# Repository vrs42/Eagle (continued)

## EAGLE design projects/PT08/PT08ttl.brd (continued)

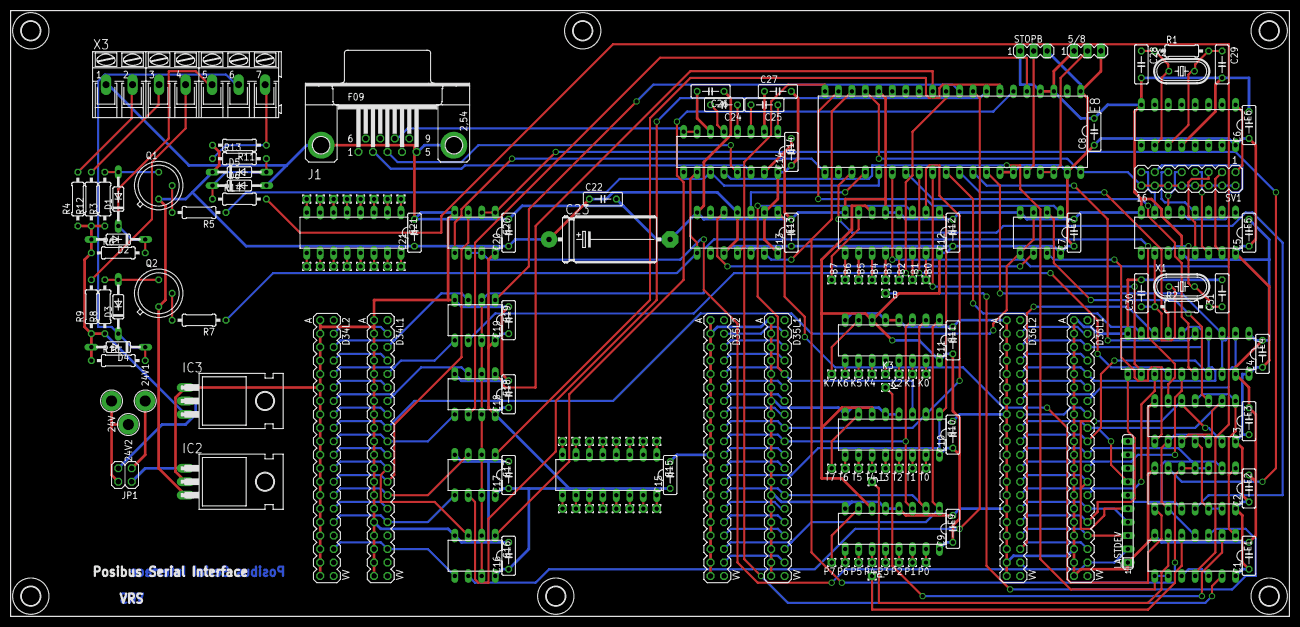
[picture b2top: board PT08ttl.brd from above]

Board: 2 copper layers, 241.3 x 114.3 mm, 168 parts (0 on the bottom side), 198 nets.

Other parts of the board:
U$1, U$2, U$3, U$4, U$5, U$6: 3,6

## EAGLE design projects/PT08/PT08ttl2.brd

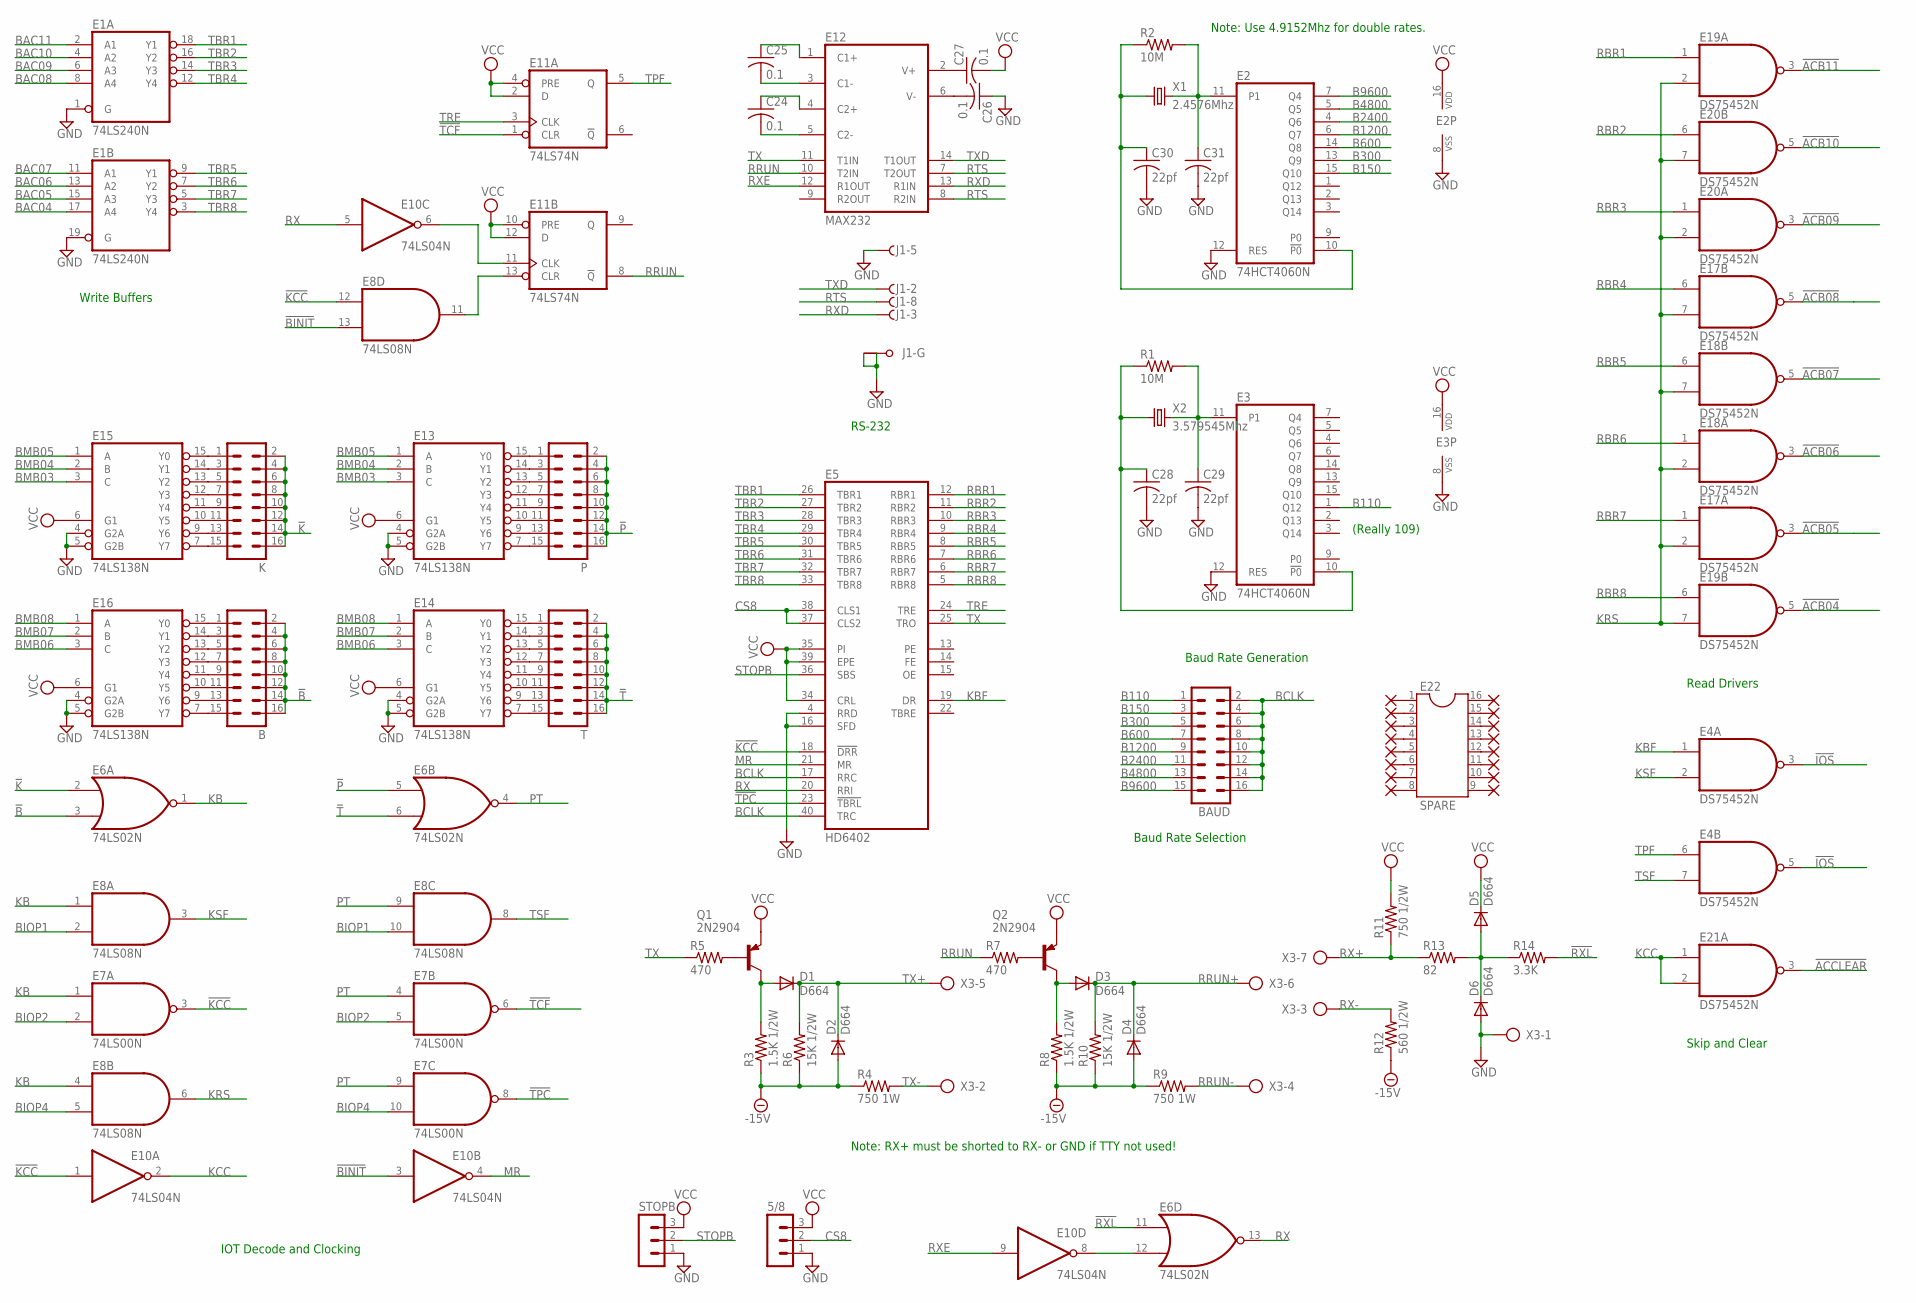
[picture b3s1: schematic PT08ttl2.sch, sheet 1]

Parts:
5/8: MA03-1
B: MA08-2
BAUD: MA08-2
C24, C25, C26, C27: 0.1; C050-025X075
C28, C29, C30, C31: 22pf; C050-025X075
D1, D2, D3, D4, D5, D6: D664; DO35-10
E1: 74LS240N; DIL20
E2, E3: 74HCT4060N; DIL16
E4, E17, E18, E19, E20, E21: DS75452N; DIL08
E5: HD6402; DIL40
E6: 74LS02N; DIL14
E7: 74LS00N; DIL14
E8: 74LS08N; DIL14
E10: 74LS04N; DIL14
E11: 74LS74N; DIL14
E12: MAX232; DIL16
E13, E14, E15, E16: 74LS138N; DIL16
E22: SPARE; DIL16
J1: F09HPS; F09HP
K: MA08-2
P: MA08-2
PAD18, PAD19, PAD28, PAD29, PAD30, PAD31, PAD32, PAD33, PAD34, PAD35, PAD36, PAD37, PAD38, PAD39, PAD40, PAD41: 1,6/0,8
Q1, Q2: 2N2904; TO39
R1, R2: 10M; 0207/10
R3, R8: 1.5K 1/2W; 0207/10
R4, R9: 750 1W; 0207/10
R5, R7: 470; 0207/10
R6, R10: 15K 1/2W; 0207/10
R11: 750 1/2W; 0207/10
R12: 560 1/2W; 0207/10
R13: 82; 0207/10
R14: 3.3K; 0207/10
STOPB: MA03-1
T: MA08-2
X1: 2.4576Mhz; HC49U-V
X2: 3.579545Mhz; HC49U-V
X3: AK300/7

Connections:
!ACB04: E19.5 (O); also elsewhere on the board
!ACB05: E17.3 (O); also elsewhere on the board
!ACB06: E18.3 (O); also elsewhere on the board
!ACB07: E18.5 (O); also elsewhere on the board
!ACB08: E17.5 (O); also elsewhere on the board
!ACB09: E20.3 (O); also elsewhere on the board
!ACB10: E20.5 (O); also elsewhere on the board
!ACB11: E19.3 (O); also elsewhere on the board
!ACCLEAR: E21.3 (O); also elsewhere on the board
!B: B.2, B.4, B.6, B.8, B.10, B.12, B.14, B.16, E6.3 (I1)
!BINIT: E8.13 (I1), E10.3 (I); also elsewhere on the board
!IOS: E4.3 (O), E4.5 (O); also elsewhere on the board
!K: E6.2 (I0), K.2, K.4, K.6, K.8, K.10, K.12, K.14, K.16
!KCC: E5.18 (!DRR), E7.3 (O), E8.12 (I0), E10.1 (I)
!P: E6.5 (I0), P.2, P.4, P.6, P.8, P.10, P.12, P.14, P.16
!RXL: E6.11 (I0), R14.2
!T: E6.6 (I1), T.2, T.4, T.6, T.8, T.10, T.12, T.14, T.16
!TCF: E7.6 (O), E11.1 (CLR)
!TPC: E5.23 (!TBRL), E7.8 (O)
-15V: D2.A, D4.A, R3.1, R4.1, R6.1, R8.1, R9.1, R10.1, R12.1; also elsewhere on the board
B110: BAUD.1, E3.1 (Q12)
B150: BAUD.3, E2.15 (Q10)
B300: BAUD.5, E2.13 (Q9)
B600: BAUD.7, E2.14 (Q8)
B1200: BAUD.9, E2.6 (Q7)
B2400: BAUD.11, E2.4 (Q6)
B4800: BAUD.13, E2.5 (Q5)
B9600: BAUD.15, E2.7 (Q4)
BAC04: E1.17 (A4); also elsewhere on the board
BAC05: E1.15 (A3); also elsewhere on the board
BAC06: E1.13 (A2); also elsewhere on the board
BAC07: E1.11 (A1); also elsewhere on the board
BAC08: E1.8 (A4); also elsewhere on the board
BAC09: E1.6 (A3); also elsewhere on the board
BAC10: E1.4 (A2); also elsewhere on the board
BAC11: E1.2 (A1); also elsewhere on the board
BCLK: BAUD.2, BAUD.4, BAUD.6, BAUD.8, BAUD.10, BAUD.12, BAUD.14, BAUD.16, E5.17 (RRC), E5.40 (TRC)
BIOP1: E8.2 (I1), E8.10 (I1); also elsewhere on the board
BIOP2: E7.2 (I1), E7.5 (I1); also elsewhere on the board
BIOP4: E7.10 (I1), E8.5 (I1); also elsewhere on the board
BMB03: E13.3 (C), E15.3 (C); also elsewhere on the board
BMB04: E13.2 (B), E15.2 (B); also elsewhere on the board
BMB05: E13.1 (A), E15.1 (A); also elsewhere on the board
BMB06: E14.3 (C), E16.3 (C); also elsewhere on the board
BMB07: E14.2 (B), E16.2 (B); also elsewhere on the board
BMB08: E14.1 (A), E16.1 (A); also elsewhere on the board
CS8: 5/8.2, E5.37 (CLS2), E5.38 (CLS1)
GND: 5/8.1, C26.1, C28.2, C29.2, C30.2, C31.2, D6.A, E1.1 (G), E1.10 (GND), E1.19 (G), E2.8 (VSS), E2.12 (RES), E3.8 (VSS), E3.12 (RES), E4.4 (GND), E5.3 (GND), E5.4 (RRD), E5.16 (SFD), E6.7 (GND), E7.7 (GND), E8.7 (GND), E10.7 (GND), E11.7 (GND), E12.15 (GND), E13.4 (G2A), E13.5 (G2B), E13.8 (GND), E14.4 (G2A), E14.5 (G2B), E14.8 (GND), E15.4 (G2A), E15.5 (G2B), E15.8 (GND), E16.4 (G2A), E16.5 (G2B), E16.8 (GND), E17.4 (GND), E18.4 (GND), E19.4 (GND), E20.4 (GND), E21.4 (GND), J1.5 (F), J1.G1, J1.G2, STOPB.1, X3.1; also elsewhere on the board
KB: E6.1 (O), E7.1 (I0), E8.1 (I0), E8.4 (I0)
KBF: E4.1 (I0), E5.19 (DR)
KCC: E10.2 (O), E21.1 (I0), E21.2 (I1)
KRS: E8.6 (O), E17.2 (I1), E17.7 (I1), E18.2 (I1), E18.7 (I1), E19.2 (I1), E19.7 (I1), E20.2 (I1), E20.7 (I1)
KSF: E4.2 (I1), E8.3 (O)
MR: E5.21 (MR), E10.4 (O)
unnamed: B.13, E16.9 (Y6)
unnamed: B.1, E16.15 (Y0)
unnamed: B.3, E16.14 (Y1)
unnamed: B.5, E16.13 (Y2)
unnamed: B.7, E16.12 (Y3)
unnamed: B.9, E16.11 (Y4)
unnamed: B.11, E16.10 (Y5)
unnamed: B.15, E16.7 (Y7)
unnamed: C29.1, E3.11 (P1), R1.2, X2.2
unnamed: C28.1, E3.10 (!P0), R1.1, X2.1
unnamed: C26.2, E12.6 (V-)
unnamed: C27.1, E12.2 (V+)
unnamed: Q1.2 (B), R5.2
unnamed: D1.A, Q1.3 (C), R3.2
unnamed: Q2.2 (B), R7.2
unnamed: D3.A, Q2.3 (C), R8.2
unnamed: C24.2, E12.5 (C2-)
unnamed: C30.1, E2.10 (!P0), R2.1, X1.1
unnamed: D5.A, D6.C, R13.2, R14.1
unnamed: C31.1, E2.11 (P1), R2.2, X1.2
unnamed: E8.11 (O), E11.13 (CLR)
unnamed: E6.12 (I1), E10.8 (O)
unnamed: E10.6 (O), E11.11 (CLK)
unnamed: C25.2, E12.3 (C1-)
unnamed: E22.1, PAD18.1
unnamed: E22.2, PAD19.1
unnamed: E22.3, PAD28.1
unnamed: C24.1, E12.4 (C2+)
unnamed: C25.1, E12.1 (C1+)
unnamed: E14.15 (Y0), T.1
unnamed: E22.4, PAD29.1
unnamed: E22.5, PAD30.1
unnamed: E22.6, PAD31.1
unnamed: E22.7, PAD32.1
unnamed: E22.8, PAD33.1
unnamed: E22.16, PAD34.1
unnamed: E22.15, PAD35.1
unnamed: E22.14, PAD36.1
unnamed: E22.13, PAD37.1
unnamed: E22.12, PAD38.1
unnamed: E22.11, PAD39.1
unnamed: E22.10, PAD40.1
unnamed: E22.9, PAD41.1
unnamed: E15.15 (Y0), K.1
unnamed: E15.14 (Y1), K.3
unnamed: E15.13 (Y2), K.5
unnamed: E15.12 (Y3), K.7
unnamed: E15.11 (Y4), K.9
unnamed: E15.10 (Y5), K.11
unnamed: E15.7 (Y7), K.15
unnamed: E15.9 (Y6), K.13
unnamed: E14.14 (Y1), T.3
unnamed: E14.13 (Y2), T.5
unnamed: E14.12 (Y3), T.7
unnamed: E14.11 (Y4), T.9
unnamed: E14.10 (Y5), T.11
unnamed: E14.7 (Y7), T.15
unnamed: E14.9 (Y6), T.13
unnamed: E13.15 (Y0), P.1
unnamed: E13.14 (Y1), P.3
unnamed: E13.13 (Y2), P.5
unnamed: E13.12 (Y3), P.7
unnamed: E13.11 (Y4), P.9
unnamed: E13.10 (Y5), P.11
unnamed: E13.7 (Y7), P.15
unnamed: E13.9 (Y6), P.13
PT: E6.4 (O), E7.4 (I0), E7.9 (I0), E8.9 (I0)
RBR1: E5.12 (RBR1), E19.1 (I0)
RBR2: E5.11 (RBR2), E20.6 (I0)
RBR3: E5.10 (RBR3), E20.1 (I0)
RBR4: E5.9 (RBR4), E17.6 (I0)
RBR5: E5.8 (RBR5), E18.6 (I0)
RBR6: E5.7 (RBR6), E18.1 (I0)
RBR7: E5.6 (RBR7), E17.1 (I0)
RBR8: E5.5 (RBR8), E19.6 (I0)
RRUN: E11.8 (!Q), E12.10 (T2IN), R7.1
RRUN+: D3.C, D4.C, R10.2, X3.6
RRUN-: R9.2, X3.4
RTS: E12.7 (T2OUT), E12.8 (R2IN), J1.8 (F)
RX: E5.20 (RRI), E6.13 (O), E10.5 (I)
RX+: R11.1, R13.1, X3.7
RX-: R12.2, X3.3
RXD: E12.13 (R1IN), J1.3 (F)
RXE: E10.9 (I), E12.12 (R1OUT)
STOPB: E5.36 (SBS), STOPB.2
TBR1: E1.18 (Y1), E5.26 (TBR1)
TBR2: E1.16 (Y2), E5.27 (TBR2)
TBR3: E1.14 (Y3), E5.28 (TBR3)
TBR4: E1.12 (Y4), E5.29 (TBR4)
TBR5: E1.9 (Y1), E5.30 (TBR5)
TBR6: E1.7 (Y2), E5.31 (TBR6)
TBR7: E1.5 (Y3), E5.32 (TBR7)
TBR8: E1.3 (Y4), E5.33 (TBR8)
TPF: E4.6 (I0), E11.5 (Q)
TRE: E5.24 (TRE), E11.3 (CLK)
TSF: E4.7 (I1), E8.8 (O)
TX: E5.25 (TRO), E12.11 (T1IN), R5.1
TX+: D1.C, D2.C, R6.2, X3.5
TX-: R4.2, X3.2
TXD: E12.14 (T1OUT), J1.2 (F)
VCC: 5/8.3, C27.2, D5.C, E1.20 (VCC), E2.16 (VDD), E3.16 (VDD), E4.8 (VCC), E5.1 (VCC), E5.34 (CRL), E5.35 (PI), E5.39 (EPE), E6.14 (VCC), E7.14 (VCC), E8.14 (VCC), E10.14 (VCC), E11.2 (D), E11.4 (PRE), E11.10 (PRE), E11.12 (D), E11.14 (VCC), E12.16 (VCC), E13.6 (G1), E13.16 (VCC), E14.6 (G1), E14.16 (VCC), E15.6 (G1), E15.16 (VCC), E16.6 (G1), E16.16 (VCC), E17.8 (VCC), E18.8 (VCC), E19.8 (VCC), E20.8 (VCC), E21.8 (VCC), Q1.1 (E), Q2.1 (E), R11.2, STOPB.3; also elsewhere on the board

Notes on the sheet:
IOT Decode and Clocking
Read Drivers
Skip and Clear
RS-232
Write Buffers
(Really 109)
Baud Rate Generation
Baud Rate Selection
Note: RX+ must be shorted to RX- or GND if TTY not used!
Note: Use 4.9152Mhz for double rates.

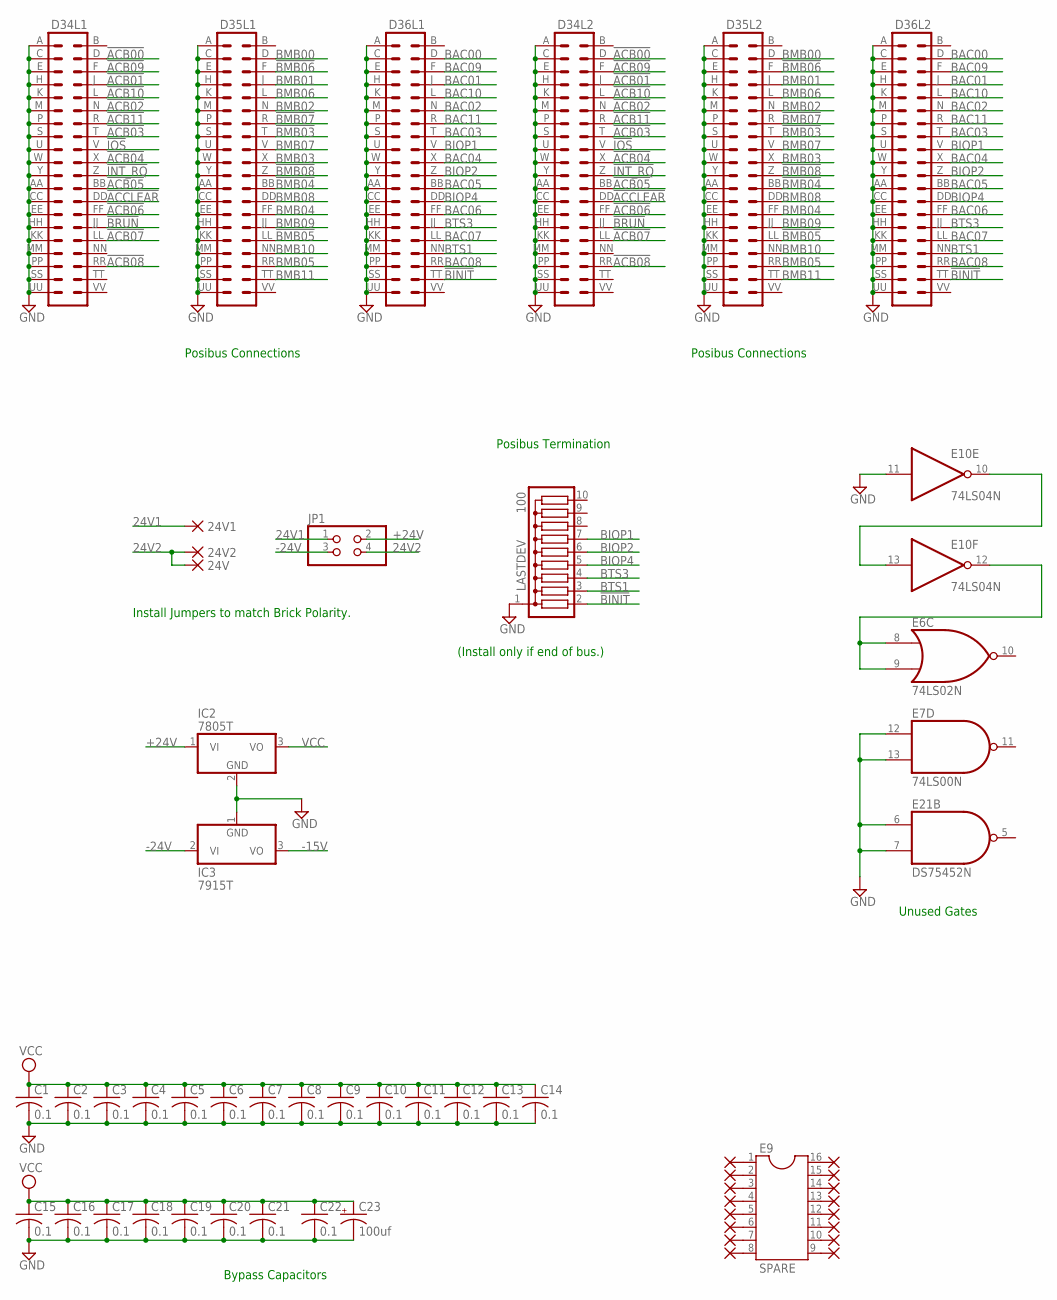
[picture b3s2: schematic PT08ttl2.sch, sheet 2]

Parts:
24V, 24V1, 24V2: PAD-0820; 0820
C1, C2, C3, C4, C5, C6, C7, C8, C9, C10, C11, C12, C13, C14, C15, C16, C17, C18, C19, C20, C21, C22: 0.1; C050-025X075
C23: 100uf; E22-9
D34L1, D34L2, D35L1, D35L2, D36L1, D36L2: DEC40PINV
E6: 74LS02N; DIL14
E7: 74LS00N; DIL14
E9: SPARE; DIL16
E10: 74LS04N; DIL14
E21: DS75452N; DIL08
IC2: 7805T; TO220H
IC3: 7915T; TO220H
JP1: PINHD-2X2; 2X02
LASTDEV: 100; SIL10
PAD1, PAD2, PAD3, PAD4, PAD5, PAD6, PAD7, PAD8, PAD9, PAD42, PAD43, PAD44, PAD45, PAD46, PAD47, PAD48: 1,6/0,8

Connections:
24V1: 24V1.P$1, JP1.1
24V2: 24V.P$1, 24V2.P$1, JP1.4
!ACB00: D34L1.D (4), D34L2.D (4)
!ACB01: D34L1.J (8), D34L2.J (8)
!ACB02: D34L1.N (12), D34L2.N (12)
!ACB03: D34L1.T (16), D34L2.T (16)
!ACB04: D34L1.X (20), D34L2.X (20); also elsewhere on the board
!ACB05: D34L1.BB (24), D34L2.BB (24); also elsewhere on the board
!ACB06: D34L1.FF (28), D34L2.FF (28); also elsewhere on the board
!ACB07: D34L1.LL (32), D34L2.LL (32); also elsewhere on the board
!ACB08: D34L1.RR (36), D34L2.RR (36); also elsewhere on the board
!ACB09: D34L1.F (6), D34L2.F (6); also elsewhere on the board
!ACB10: D34L1.L (10), D34L2.L (10); also elsewhere on the board
!ACB11: D34L1.R (14), D34L2.R (14); also elsewhere on the board
!ACCLEAR: D34L1.DD (26), D34L2.DD (26); also elsewhere on the board
!BINIT: D36L1.TT (38), D36L2.TT (38), LASTDEV.2; also elsewhere on the board
!BMB03: D35L1.T (16), D35L2.T (16)
!BMB04: D35L1.BB (24), D35L2.BB (24)
!BMB05: D35L1.LL (32), D35L2.LL (32)
!BMB06: D35L1.F (6), D35L2.F (6)
!BMB07: D35L1.R (14), D35L2.R (14)
!BMB08: D35L1.Z (22), D35L2.Z (22)
!BRUN: D34L1.JJ (30), D34L2.JJ (30)
!INT_RQ: D34L1.Z (22), D34L2.Z (22)
!IOS: D34L1.V (18), D34L2.V (18); also elsewhere on the board
+24V: IC2.1 (VI), JP1.2
-15V: IC3.3 (VO); also elsewhere on the board
-24V: IC3.2 (VI), JP1.3
BAC00: D36L1.D (4), D36L2.D (4)
BAC01: D36L1.J (8), D36L2.J (8)
BAC02: D36L1.N (12), D36L2.N (12)
BAC03: D36L1.T (16), D36L2.T (16)
BAC04: D36L1.X (20), D36L2.X (20); also elsewhere on the board
BAC05: D36L1.BB (24), D36L2.BB (24); also elsewhere on the board
BAC06: D36L1.FF (28), D36L2.FF (28); also elsewhere on the board
BAC07: D36L1.LL (32), D36L2.LL (32); also elsewhere on the board
BAC08: D36L1.RR (36), D36L2.RR (36); also elsewhere on the board
BAC09: D36L1.F (6), D36L2.F (6); also elsewhere on the board
BAC10: D36L1.L (10), D36L2.L (10); also elsewhere on the board
BAC11: D36L1.R (14), D36L2.R (14); also elsewhere on the board
BIOP1: D36L1.V (18), D36L2.V (18), LASTDEV.7; also elsewhere on the board
BIOP2: D36L1.Z (22), D36L2.Z (22), LASTDEV.6; also elsewhere on the board
BIOP4: D36L1.DD (26), D36L2.DD (26), LASTDEV.5; also elsewhere on the board
BMB00: D35L1.D (4), D35L2.D (4)
BMB01: D35L1.J (8), D35L2.J (8)
BMB02: D35L1.N (12), D35L2.N (12)
BMB03: D35L1.X (20), D35L2.X (20); also elsewhere on the board
BMB04: D35L1.FF (28), D35L2.FF (28); also elsewhere on the board
BMB05: D35L1.RR (36), D35L2.RR (36); also elsewhere on the board
BMB06: D35L1.L (10), D35L2.L (10); also elsewhere on the board
BMB07: D35L1.V (18), D35L2.V (18); also elsewhere on the board
BMB08: D35L1.DD (26), D35L2.DD (26); also elsewhere on the board
BMB09: D35L1.JJ (30), D35L2.JJ (30)
BMB10: D35L1.NN (34), D35L2.NN (34)
BMB11: D35L1.TT (38), D35L2.TT (38)
BTS1: D36L1.NN (34), D36L2.NN (34), LASTDEV.3
BTS3: D36L1.JJ (30), D36L2.JJ (30), LASTDEV.4
GND: C1.2, C2.2, C3.2, C4.2, C5.2, C6.2, C7.2, C8.2, C9.2, C10.2, C11.2, C12.2, C13.2, C14.2, C15.2, C16.2, C17.2, C18.2, C19.2, C20.2, C21.2, C22.2, C23.-, D34L1.A (1), D34L1.AA (23), D34L1.C (3), D34L1.CC (25), D34L1.E (5), D34L1.EE (27), D34L1.H (7), D34L1.HH (29), D34L1.K (9), D34L1.KK (31), D34L1.M (11), D34L1.MM (33), D34L1.P (13), D34L1.PP (35), D34L1.S (15), D34L1.SS (37), D34L1.U (17), D34L1.UU (39), D34L1.W (19), D34L1.Y (21), D34L2.A (1), D34L2.AA (23), D34L2.C (3), D34L2.CC (25), D34L2.E (5), D34L2.EE (27), D34L2.H (7), D34L2.HH (29), D34L2.K (9), D34L2.KK (31), D34L2.M (11), D34L2.MM (33), D34L2.P (13), D34L2.PP (35), D34L2.S (15), D34L2.SS (37), D34L2.U (17), D34L2.UU (39), D34L2.W (19), D34L2.Y (21), D35L1.A (1), D35L1.AA (23), D35L1.C (3), D35L1.CC (25), D35L1.E (5), D35L1.EE (27), D35L1.H (7), D35L1.HH (29), D35L1.K (9), D35L1.KK (31), D35L1.M (11), D35L1.MM (33), D35L1.P (13), D35L1.PP (35), D35L1.S (15), D35L1.SS (37), D35L1.U (17), D35L1.UU (39), D35L1.W (19), D35L1.Y (21), D35L2.A (1), D35L2.AA (23), D35L2.C (3), D35L2.CC (25), D35L2.E (5), D35L2.EE (27), D35L2.H (7), D35L2.HH (29), D35L2.K (9), D35L2.KK (31), D35L2.M (11), D35L2.MM (33), D35L2.P (13), D35L2.PP (35), D35L2.S (15), D35L2.SS (37), D35L2.U (17), D35L2.UU (39), D35L2.W (19), D35L2.Y (21), D36L1.A (1), D36L1.AA (23), D36L1.C (3), D36L1.CC (25), D36L1.E (5), D36L1.EE (27), D36L1.H (7), D36L1.HH (29), D36L1.K (9), D36L1.KK (31), D36L1.M (11), D36L1.MM (33), D36L1.P (13), D36L1.PP (35), D36L1.S (15), D36L1.SS (37), D36L1.U (17), D36L1.UU (39), D36L1.W (19), D36L1.Y (21), D36L2.A (1), D36L2.AA (23), D36L2.C (3), D36L2.CC (25), D36L2.E (5), D36L2.EE (27), D36L2.H (7), D36L2.HH (29), D36L2.K (9), D36L2.KK (31), D36L2.M (11), D36L2.MM (33), D36L2.P (13), D36L2.PP (35), D36L2.S (15), D36L2.SS (37), D36L2.U (17), D36L2.UU (39), D36L2.W (19), D36L2.Y (21), E6.7 (GND), E7.7 (GND), E7.12 (I0), E7.13 (I1), E10.7 (GND), E10.11 (I), E21.4 (GND), E21.6 (I0), E21.7 (I1), IC2.2 (GND), IC3.1 (GND), LASTDEV.1; also elsewhere on the board
unnamed: E9.1, PAD1.1
unnamed: E9.2, PAD2.1
unnamed: E9.3, PAD3.1
unnamed: E9.4, PAD4.1
unnamed: E9.5, PAD5.1
unnamed: E10.10 (O), E10.13 (I)
unnamed: E9.6, PAD6.1
unnamed: E9.7, PAD7.1
unnamed: E9.8, PAD8.1
unnamed: E9.16, PAD9.1
unnamed: E9.15, PAD42.1
unnamed: E9.14, PAD43.1
unnamed: E9.13, PAD44.1
unnamed: E9.12, PAD45.1
unnamed: E9.11, PAD46.1
unnamed: E9.10, PAD47.1
unnamed: E9.9, PAD48.1
unnamed: E6.8 (I0), E6.9 (I1), E10.12 (O)
VCC: C1.1, C2.1, C3.1, C4.1, C5.1, C6.1, C7.1, C8.1, C9.1, C10.1, C11.1, C12.1, C13.1, C14.1, C15.1, C16.1, C17.1, C18.1, C19.1, C20.1, C21.1, C22.1, C23.+, E6.14 (VCC), E7.14 (VCC), E10.14 (VCC), E21.8 (VCC), IC2.3 (VO); also elsewhere on the board

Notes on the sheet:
Bypass Capacitors
Posibus Connections
Posibus Termination
(Install only if end of bus.)
Install Jumpers to match Brick Polarity.
Unused Gates

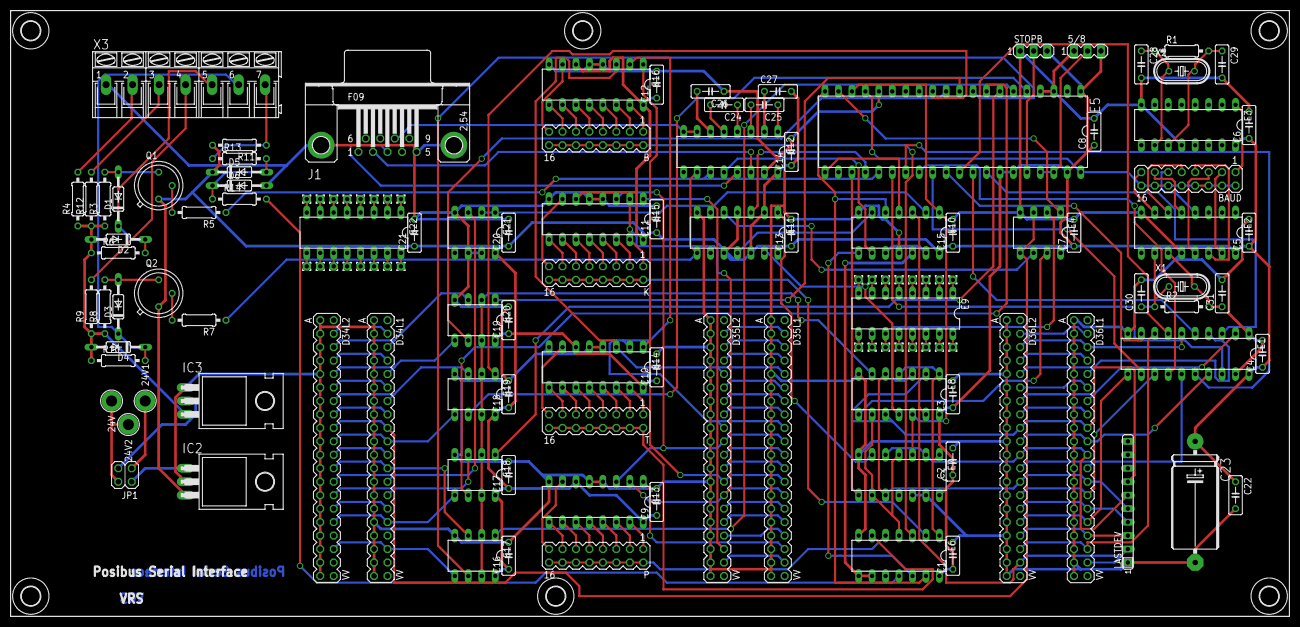
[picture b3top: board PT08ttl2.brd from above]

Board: 2 copper layers, 241.3 x 114.3 mm, 137 parts (0 on the bottom side), 201 nets.

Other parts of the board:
U$1, U$2, U$3, U$4, U$5, U$6: 3,6

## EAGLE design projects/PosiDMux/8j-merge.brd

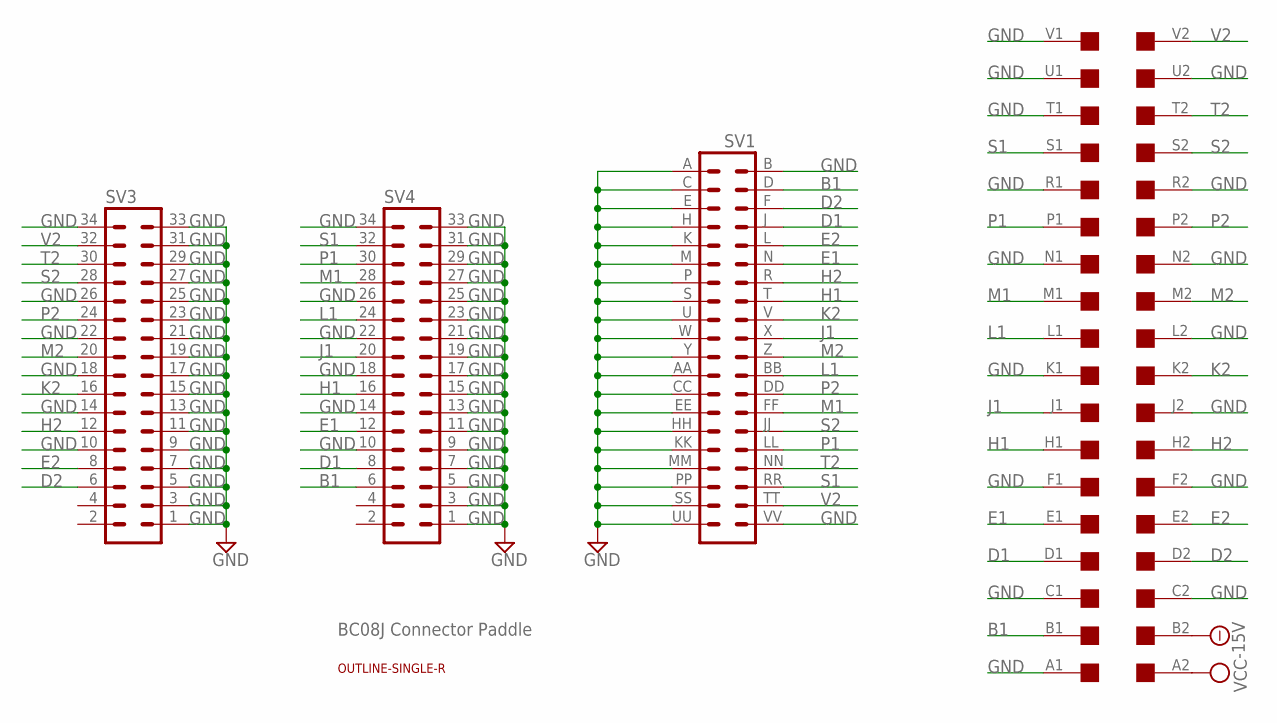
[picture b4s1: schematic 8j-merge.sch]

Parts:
SV1: DEC40PINV
SV3, SV4: MA17-2
U$1: OUTLINE-SINGLE-R; SINGLE-R
U$2: SINGLE; EDGE-CON2

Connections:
-15V: U$2.B2
B1: SV1.D (4), SV4.6, U$2.B1
D1: SV1.J (8), SV4.8, U$2.D1
D2: SV1.F (6), SV3.6, U$2.D2
E1: SV1.N (12), SV4.12, U$2.E1
E2: SV1.L (10), SV3.8, U$2.E2
GND: SV1.A (1), SV1.AA (23), SV1.B (2), SV1.C (3), SV1.CC (25), SV1.E (5), SV1.EE (27), SV1.H (7), SV1.HH (29), SV1.K (9), SV1.KK (31), SV1.M (11), SV1.MM (33), SV1.P (13), SV1.PP (35), SV1.S (15), SV1.SS (37), SV1.U (17), SV1.UU (39), SV1.VV (40), SV1.W (19), SV1.Y (21), SV3.1, SV3.3, SV3.5, SV3.7, SV3.9, SV3.10, SV3.11, SV3.13, SV3.14, SV3.15, SV3.17, SV3.18, SV3.19, SV3.21, SV3.22, SV3.23, SV3.25, SV3.26, SV3.27, SV3.29, SV3.31, SV3.33, SV3.34, SV4.1, SV4.3, SV4.5, SV4.7, SV4.9, SV4.10, SV4.11, SV4.13, SV4.14, SV4.15, SV4.17, SV4.18, SV4.19, SV4.21, SV4.22, SV4.23, SV4.25, SV4.26, SV4.27, SV4.29, SV4.31, SV4.33, SV4.34, U$2.A1, U$2.C1, U$2.C2, U$2.F1, U$2.F2, U$2.J2, U$2.K1, U$2.L2, U$2.N1, U$2.N2, U$2.R1, U$2.R2, U$2.T1, U$2.U1, U$2.U2, U$2.V1
H1: SV1.T (16), SV4.16, U$2.H1
H2: SV1.R (14), SV3.12, U$2.H2
J1: SV1.X (20), SV4.20, U$2.J1
K2: SV1.V (18), SV3.16, U$2.K2
L1: SV1.BB (24), SV4.24, U$2.L1
M1: SV1.FF (28), SV4.28, U$2.M1
M2: SV1.Z (22), SV3.20, U$2.M2
P1: SV1.LL (32), SV4.30, U$2.P1
P2: SV1.DD (26), SV3.24, U$2.P2
S1: SV1.RR (36), SV4.32, U$2.S1
S2: SV1.JJ (30), SV3.28, U$2.S2
T2: SV1.NN (34), SV3.30, U$2.T2
V2: SV1.TT (38), SV3.32, U$2.V2
VCC: U$2.A2

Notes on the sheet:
BC08J Connector Paddle

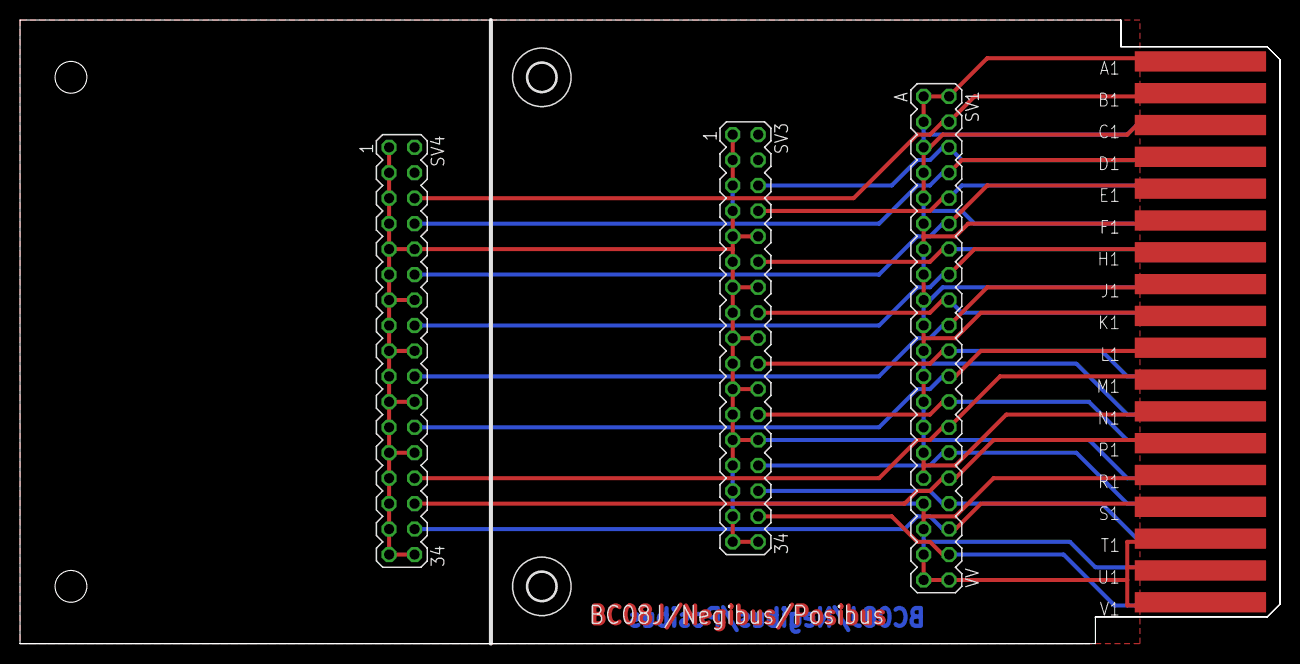
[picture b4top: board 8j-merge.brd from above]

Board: 2 copper layers, 125.7 x 62.2 mm, 7 parts (0 on the bottom side), 19 nets.

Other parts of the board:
U$3, U$4: 2,8

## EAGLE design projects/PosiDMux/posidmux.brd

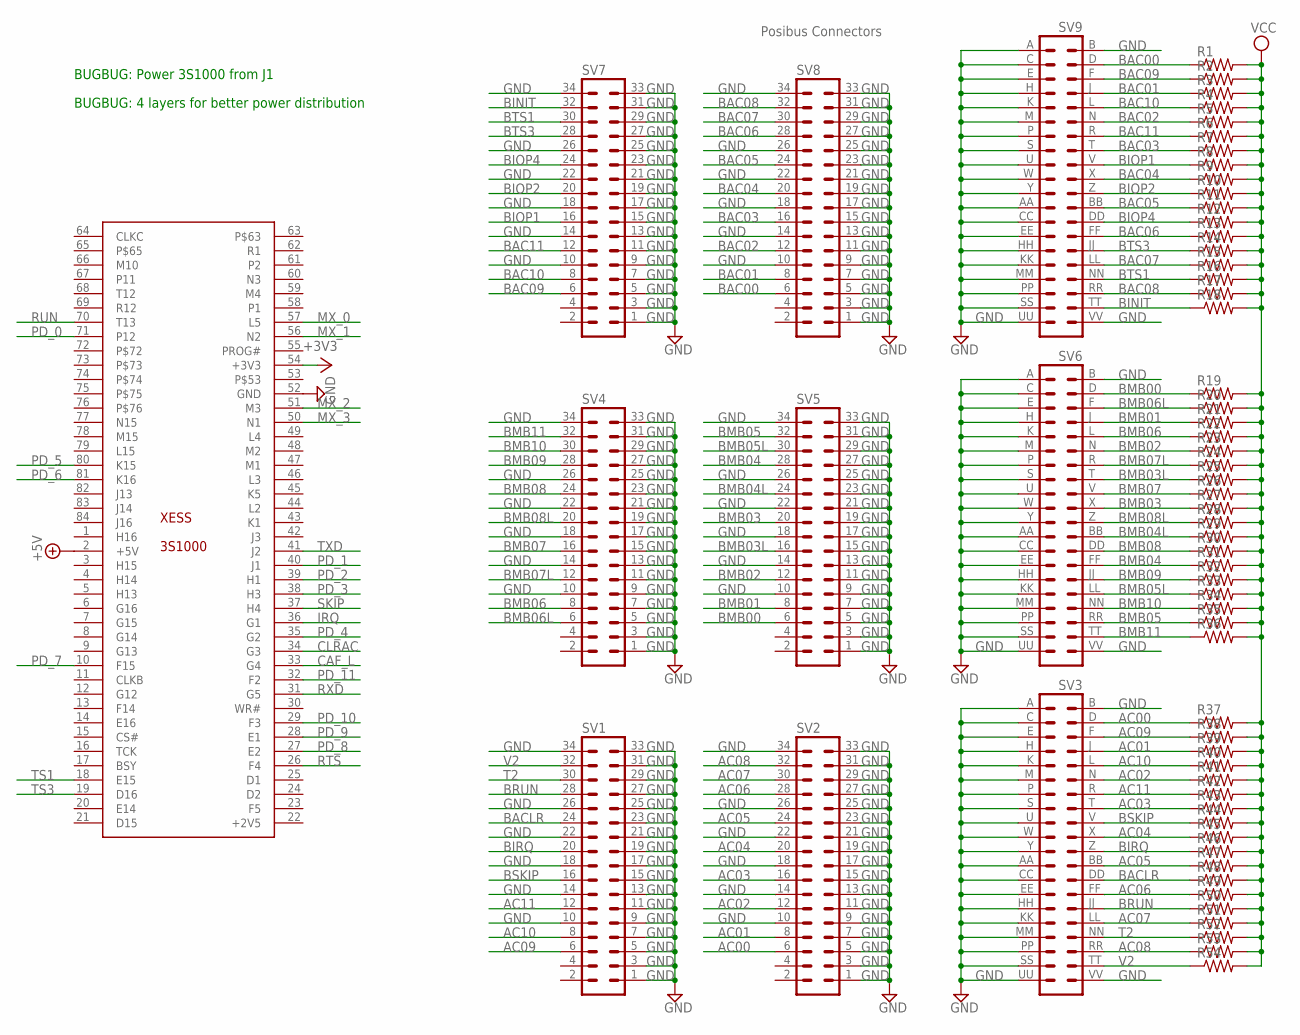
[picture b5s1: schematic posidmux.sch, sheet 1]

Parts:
R1, R2, R3, R4, R5, R6, R7, R8, R9, R10, R11, R12, R13, R14, R15, R16, R17, R18, R19, R20, R21, R22, R23, R24, R25, R26, R27, R28, R29, R30, R31, R32, R33, R34, R35, R36, R37, R38, R39, R40, R41, R42, R43, R44, R45, R46, R47, R48, R49, R50, R51, R52, R53, R54: R-US_0207/10; 0207/10
SV1, SV2, SV4, SV5, SV7, SV8: MA17-2
SV3, SV6, SV9: DEC40PINV
XESS: 3S1000

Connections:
+2V5: XESS.22 (+2V5)
+3V3: XESS.54 (+3V3); also elsewhere on the board
+5V: XESS.2 (+5V)
AC00: R37.1, SV2.6, SV3.D (4); also elsewhere on the board
AC01: R39.1, SV2.8, SV3.J (8); also elsewhere on the board
AC02: R41.1, SV2.12, SV3.N (12); also elsewhere on the board
AC03: R43.1, SV2.16, SV3.T (16); also elsewhere on the board
AC04: R45.1, SV2.20, SV3.X (20); also elsewhere on the board
AC05: R47.1, SV2.24, SV3.BB (24); also elsewhere on the board
AC06: R49.1, SV2.28, SV3.FF (28); also elsewhere on the board
AC07: R51.1, SV2.30, SV3.LL (32); also elsewhere on the board
AC08: R53.1, SV2.32, SV3.RR (36); also elsewhere on the board
AC09: R38.1, SV1.6, SV3.F (6); also elsewhere on the board
AC10: R40.1, SV1.8, SV3.L (10); also elsewhere on the board
AC11: R42.1, SV1.12, SV3.R (14); also elsewhere on the board
BAC00: R1.1, SV8.6, SV9.D (4); also elsewhere on the board
BAC01: R3.1, SV8.8, SV9.J (8); also elsewhere on the board
BAC02: R5.1, SV8.12, SV9.N (12); also elsewhere on the board
BAC03: R7.1, SV8.16, SV9.T (16); also elsewhere on the board
BAC04: R9.1, SV8.20, SV9.X (20); also elsewhere on the board
BAC05: R11.1, SV8.24, SV9.BB (24); also elsewhere on the board
BAC06: R13.1, SV8.28, SV9.FF (28); also elsewhere on the board
BAC07: R15.1, SV8.30, SV9.LL (32); also elsewhere on the board
BAC08: R17.1, SV8.32, SV9.RR (36); also elsewhere on the board
BAC09: R2.1, SV7.6, SV9.F (6); also elsewhere on the board
BAC10: R4.1, SV7.8, SV9.L (10); also elsewhere on the board
BAC11: R6.1, SV7.12, SV9.R (14); also elsewhere on the board
BACLR: R48.1, SV1.24, SV3.DD (26); also elsewhere on the board
BINIT: R18.1, SV7.32, SV9.TT (38); also elsewhere on the board
BIOP1: R8.1, SV7.16, SV9.V (18); also elsewhere on the board
BIOP2: R10.1, SV7.20, SV9.Z (22); also elsewhere on the board
BIOP4: R12.1, SV7.24, SV9.DD (26); also elsewhere on the board
BIRQ: R46.1, SV1.20, SV3.Z (22); also elsewhere on the board
BMB00: R19.1, SV5.6, SV6.D (4); also elsewhere on the board
BMB01: R21.1, SV5.8, SV6.J (8); also elsewhere on the board
BMB02: R23.1, SV5.12, SV6.N (12); also elsewhere on the board
BMB03: R27.1, SV5.20, SV6.X (20); also elsewhere on the board
BMB03L: R25.1, SV5.16, SV6.T (16); also elsewhere on the board
BMB04: R31.1, SV5.28, SV6.FF (28); also elsewhere on the board
BMB04L: R29.1, SV5.24, SV6.BB (24); also elsewhere on the board
BMB05: R35.1, SV5.32, SV6.RR (36); also elsewhere on the board
BMB05L: R33.1, SV5.30, SV6.LL (32); also elsewhere on the board
BMB06: R22.1, SV4.8, SV6.L (10); also elsewhere on the board
BMB06L: R20.1, SV4.6, SV6.F (6); also elsewhere on the board
BMB07: R26.1, SV4.16, SV6.V (18); also elsewhere on the board
BMB07L: R24.1, SV4.12, SV6.R (14); also elsewhere on the board
BMB08: R30.1, SV4.24, SV6.DD (26); also elsewhere on the board
BMB08L: R28.1, SV4.20, SV6.Z (22); also elsewhere on the board
BMB09: R32.1, SV4.28, SV6.JJ (30); also elsewhere on the board
BMB10: R34.1, SV4.30, SV6.NN (34); also elsewhere on the board
BMB11: R36.1, SV4.32, SV6.TT (38); also elsewhere on the board
BRUN: R50.1, SV1.28, SV3.JJ (30); also elsewhere on the board
BSKIP: R44.1, SV1.16, SV3.V (18); also elsewhere on the board
BTS1: R16.1, SV7.30, SV9.NN (34); also elsewhere on the board
BTS3: R14.1, SV7.28, SV9.JJ (30); also elsewhere on the board
CAF_L: XESS.33 (G4); also elsewhere on the board
CLRAC: XESS.34 (G3); also elsewhere on the board
GND: SV1.1, SV1.3, SV1.5, SV1.7, SV1.9, SV1.10, SV1.11, SV1.13, SV1.14, SV1.15, SV1.17, SV1.18, SV1.19, SV1.21, SV1.22, SV1.23, SV1.25, SV1.26, SV1.27, SV1.29, SV1.31, SV1.33, SV1.34, SV2.1, SV2.3, SV2.5, SV2.7, SV2.9, SV2.10, SV2.11, SV2.13, SV2.14, SV2.15, SV2.17, SV2.18, SV2.19, SV2.21, SV2.22, SV2.23, SV2.25, SV2.26, SV2.27, SV2.29, SV2.31, SV2.33, SV2.34, SV3.A (1), SV3.AA (23), SV3.B (2), SV3.C (3), SV3.CC (25), SV3.E (5), SV3.EE (27), SV3.H (7), SV3.HH (29), SV3.K (9), SV3.KK (31), SV3.M (11), SV3.MM (33), SV3.P (13), SV3.PP (35), SV3.S (15), SV3.SS (37), SV3.U (17), SV3.UU (39), SV3.VV (40), SV3.W (19), SV3.Y (21), SV4.1, SV4.3, SV4.5, SV4.7, SV4.9, SV4.10, SV4.11, SV4.13, SV4.14, SV4.15, SV4.17, SV4.18, SV4.19, SV4.21, SV4.22, SV4.23, SV4.25, SV4.26, SV4.27, SV4.29, SV4.31, SV4.33, SV4.34, SV5.1, SV5.3, SV5.5, SV5.7, SV5.9, SV5.10, SV5.11, SV5.13, SV5.14, SV5.15, SV5.17, SV5.18, SV5.19, SV5.21, SV5.22, SV5.23, SV5.25, SV5.26, SV5.27, SV5.29, SV5.31, SV5.33, SV5.34, SV6.A (1), SV6.AA (23), SV6.B (2), SV6.C (3), SV6.CC (25), SV6.E (5), SV6.EE (27), SV6.H (7), SV6.HH (29), SV6.K (9), SV6.KK (31), SV6.M (11), SV6.MM (33), SV6.P (13), SV6.PP (35), SV6.S (15), SV6.SS (37), SV6.U (17), SV6.UU (39), SV6.VV (40), SV6.W (19), SV6.Y (21), SV7.1, SV7.3, SV7.5, SV7.7, SV7.9, SV7.10, SV7.11, SV7.13, SV7.14, SV7.15, SV7.17, SV7.18, SV7.19, SV7.21, SV7.22, SV7.23, SV7.25, SV7.26, SV7.27, SV7.29, SV7.31, SV7.33, SV7.34, SV8.1, SV8.3, SV8.5, SV8.7, SV8.9, SV8.10, SV8.11, SV8.13, SV8.14, SV8.15, SV8.17, SV8.18, SV8.19, SV8.21, SV8.22, SV8.23, SV8.25, SV8.26, SV8.27, SV8.29, SV8.31, SV8.33, SV8.34, SV9.A (1), SV9.AA (23), SV9.B (2), SV9.C (3), SV9.CC (25), SV9.E (5), SV9.EE (27), SV9.H (7), SV9.HH (29), SV9.K (9), SV9.KK (31), SV9.M (11), SV9.MM (33), SV9.P (13), SV9.PP (35), SV9.S (15), SV9.SS (37), SV9.U (17), SV9.UU (39), SV9.VV (40), SV9.W (19), SV9.Y (21), XESS.52 (GND); also elsewhere on the board
IRQ: XESS.36 (G1); also elsewhere on the board
MX_0: XESS.57 (L5); also elsewhere on the board
MX_1: XESS.56 (N2); also elsewhere on the board
MX_2: XESS.51 (M3); also elsewhere on the board
MX_3: XESS.50 (N1); also elsewhere on the board
PD_0: XESS.71 (P12); also elsewhere on the board
PD_1: XESS.40 (J1); also elsewhere on the board
PD_2: XESS.39 (H1); also elsewhere on the board
PD_3: XESS.38 (H3); also elsewhere on the board
PD_4: XESS.35 (G2); also elsewhere on the board
PD_5: XESS.80 (K15); also elsewhere on the board
PD_6: XESS.81 (K16); also elsewhere on the board
PD_7: XESS.10 (F15); also elsewhere on the board
PD_8: XESS.27 (E2); also elsewhere on the board
PD_9: XESS.28 (E1); also elsewhere on the board
PD_10: XESS.29 (F3); also elsewhere on the board
PD_11: XESS.32 (F2); also elsewhere on the board
RTS: XESS.26 (F4); also elsewhere on the board
RUN: XESS.70 (T13); also elsewhere on the board
RXD: XESS.31 (G5); also elsewhere on the board
SKIP: XESS.37 (H4); also elsewhere on the board
T2: R52.1, SV1.30, SV3.NN (34)
TS1: XESS.18 (E15); also elsewhere on the board
TS3: XESS.19 (D16); also elsewhere on the board
TXD: XESS.41 (J2); also elsewhere on the board
V2: R54.1, SV1.32, SV3.TT (38)
VCC: R1.2, R2.2, R3.2, R4.2, R5.2, R6.2, R7.2, R8.2, R9.2, R10.2, R11.2, R12.2, R13.2, R14.2, R15.2, R16.2, R17.2, R18.2, R19.2, R20.2, R21.2, R22.2, R23.2, R24.2, R25.2, R26.2, R27.2, R28.2, R29.2, R30.2, R31.2, R32.2, R33.2, R34.2, R35.2, R36.2, R37.2, R38.2, R39.2, R40.2, R41.2, R42.2, R43.2, R44.2, R45.2, R46.2, R47.2, R48.2, R49.2, R50.2, R51.2, R52.2, R53.2, R54.2; also elsewhere on the board

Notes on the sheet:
Posibus Connectors
BUGBUG: Power 3S1000 from J1
BUGBUG: 4 layers for better power distribution
